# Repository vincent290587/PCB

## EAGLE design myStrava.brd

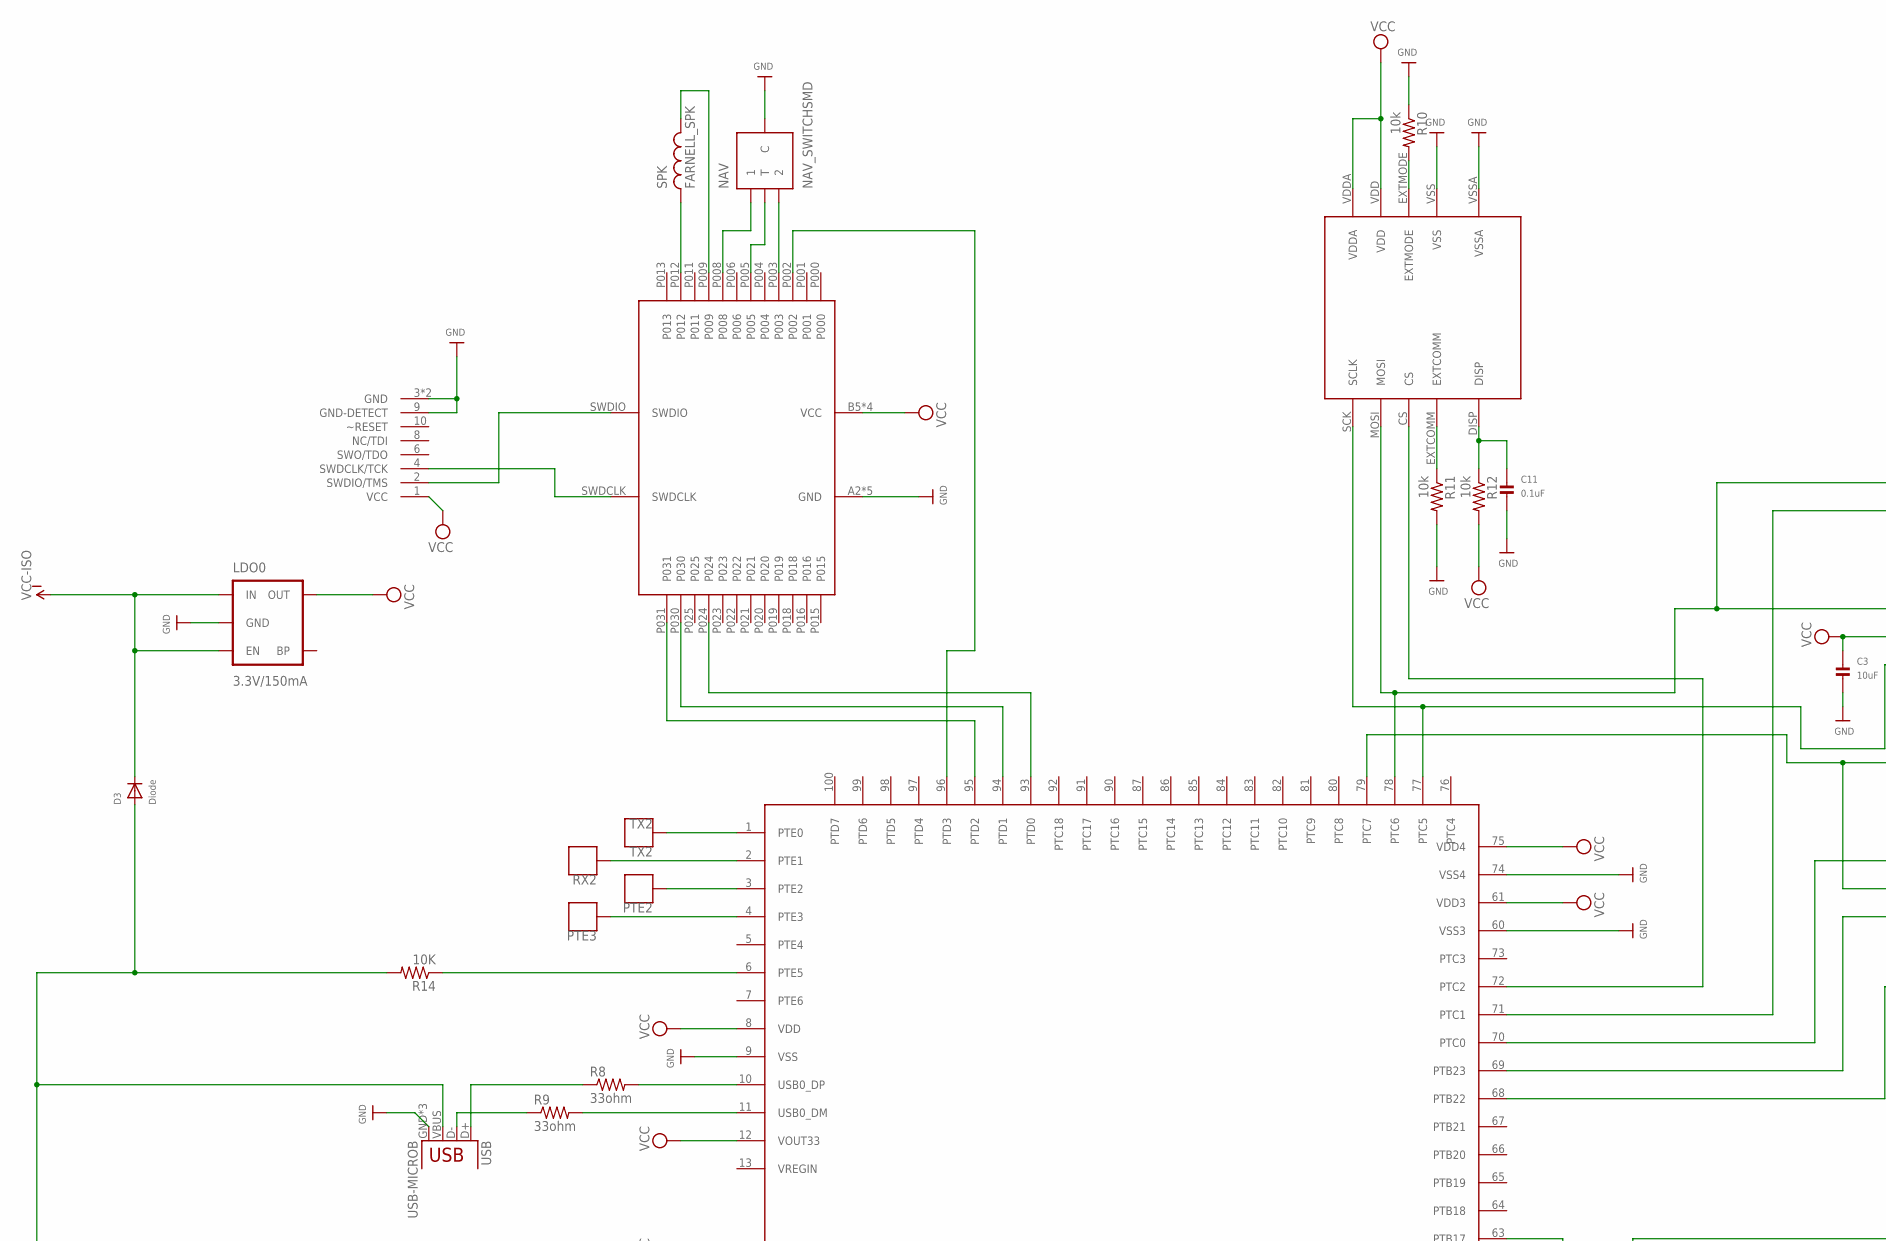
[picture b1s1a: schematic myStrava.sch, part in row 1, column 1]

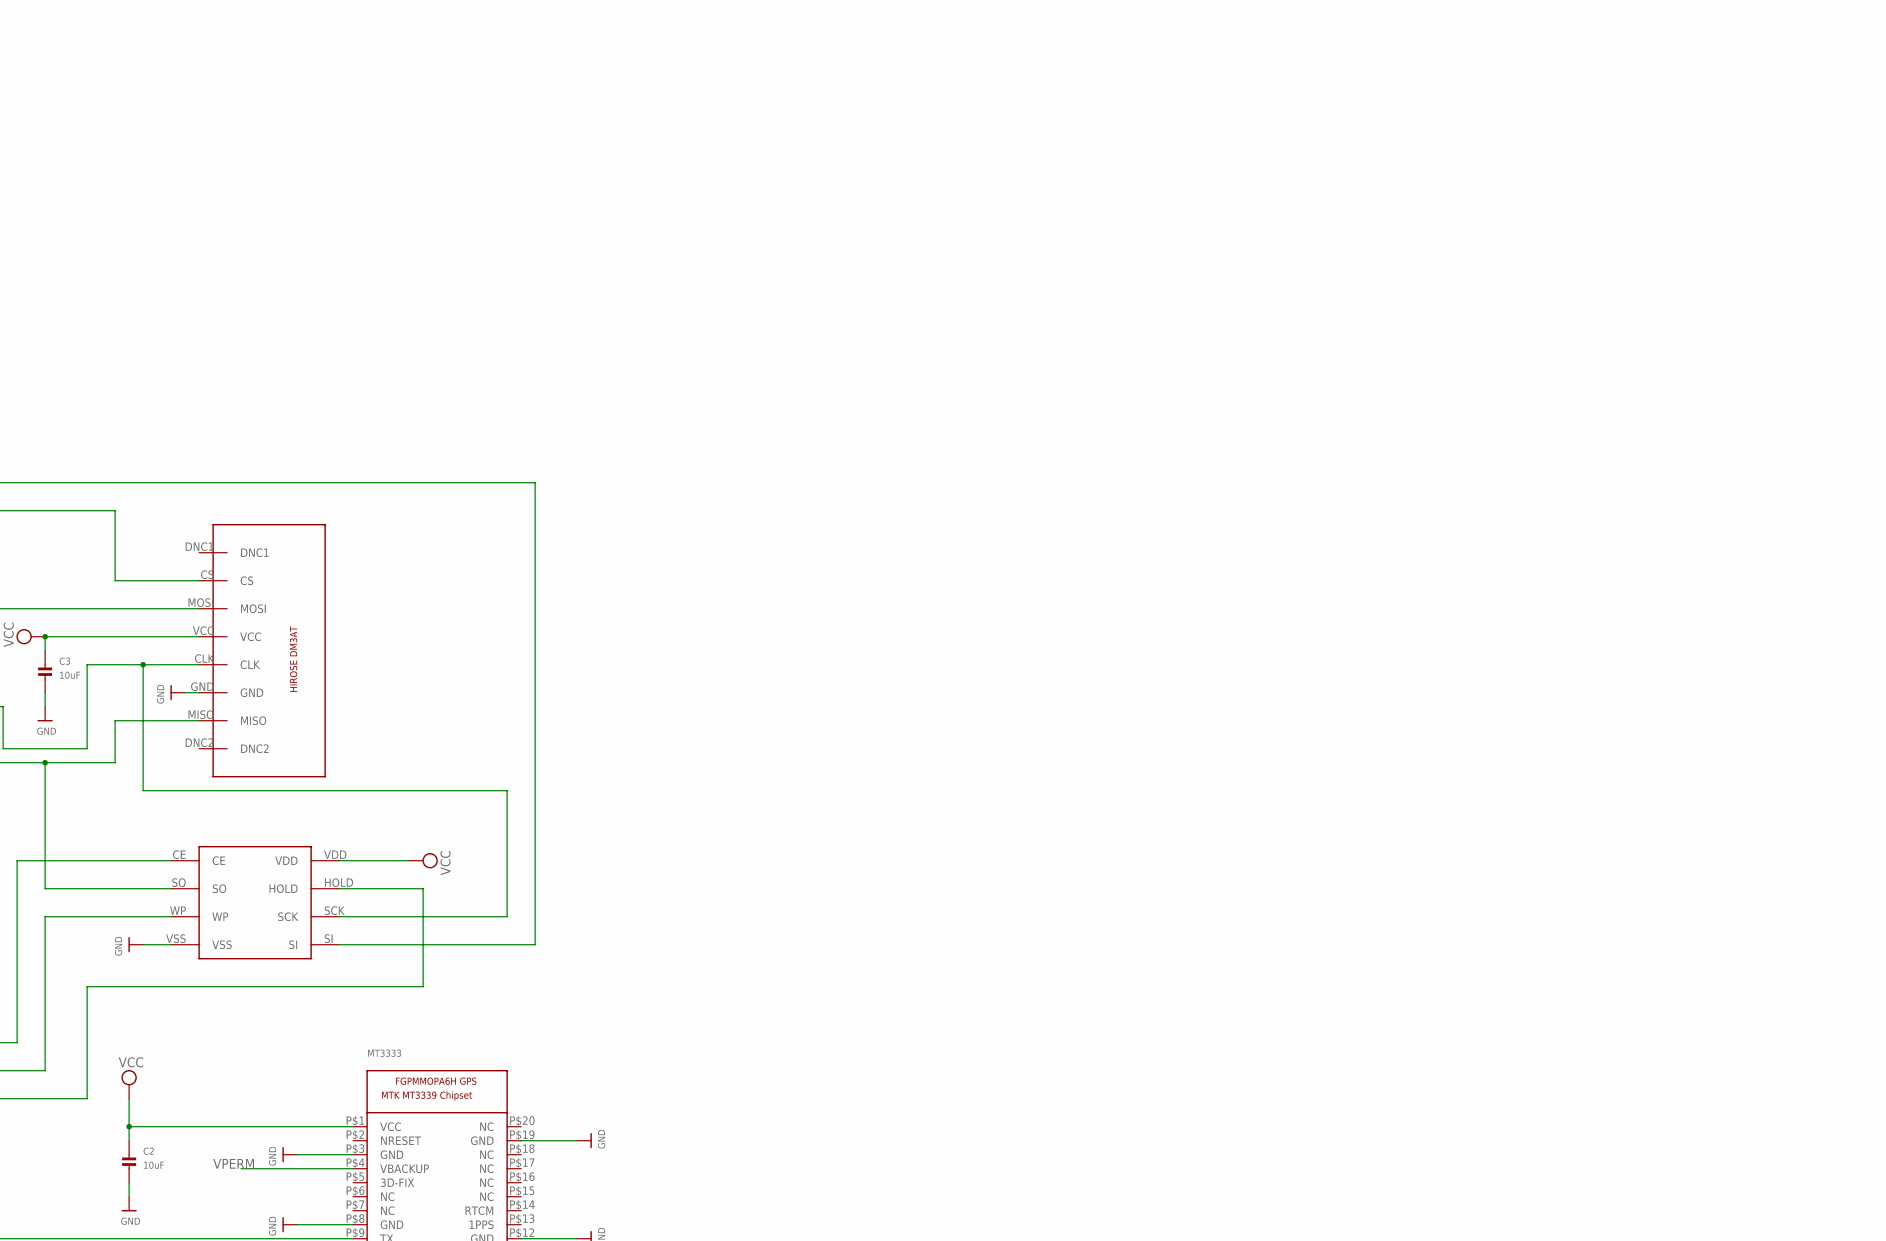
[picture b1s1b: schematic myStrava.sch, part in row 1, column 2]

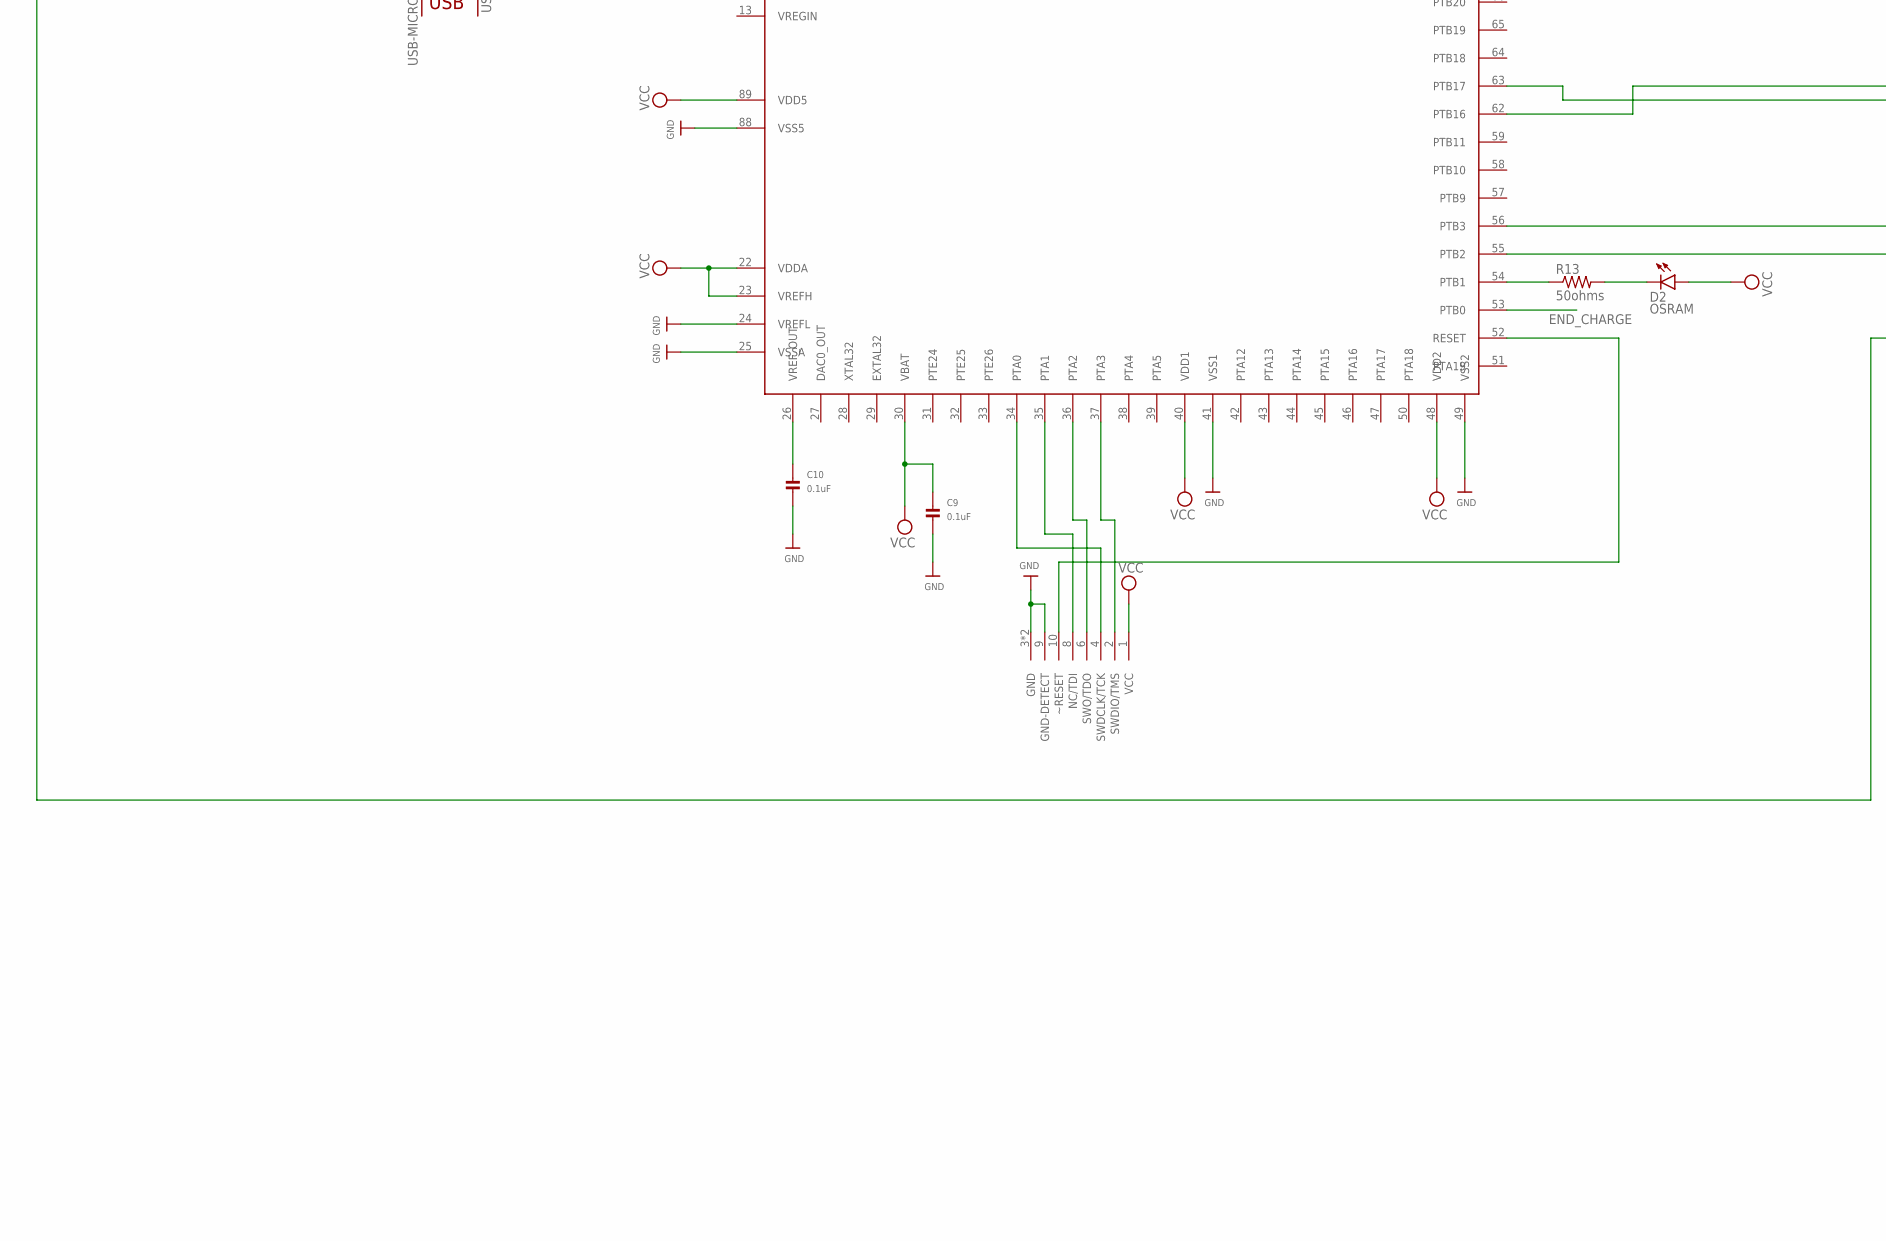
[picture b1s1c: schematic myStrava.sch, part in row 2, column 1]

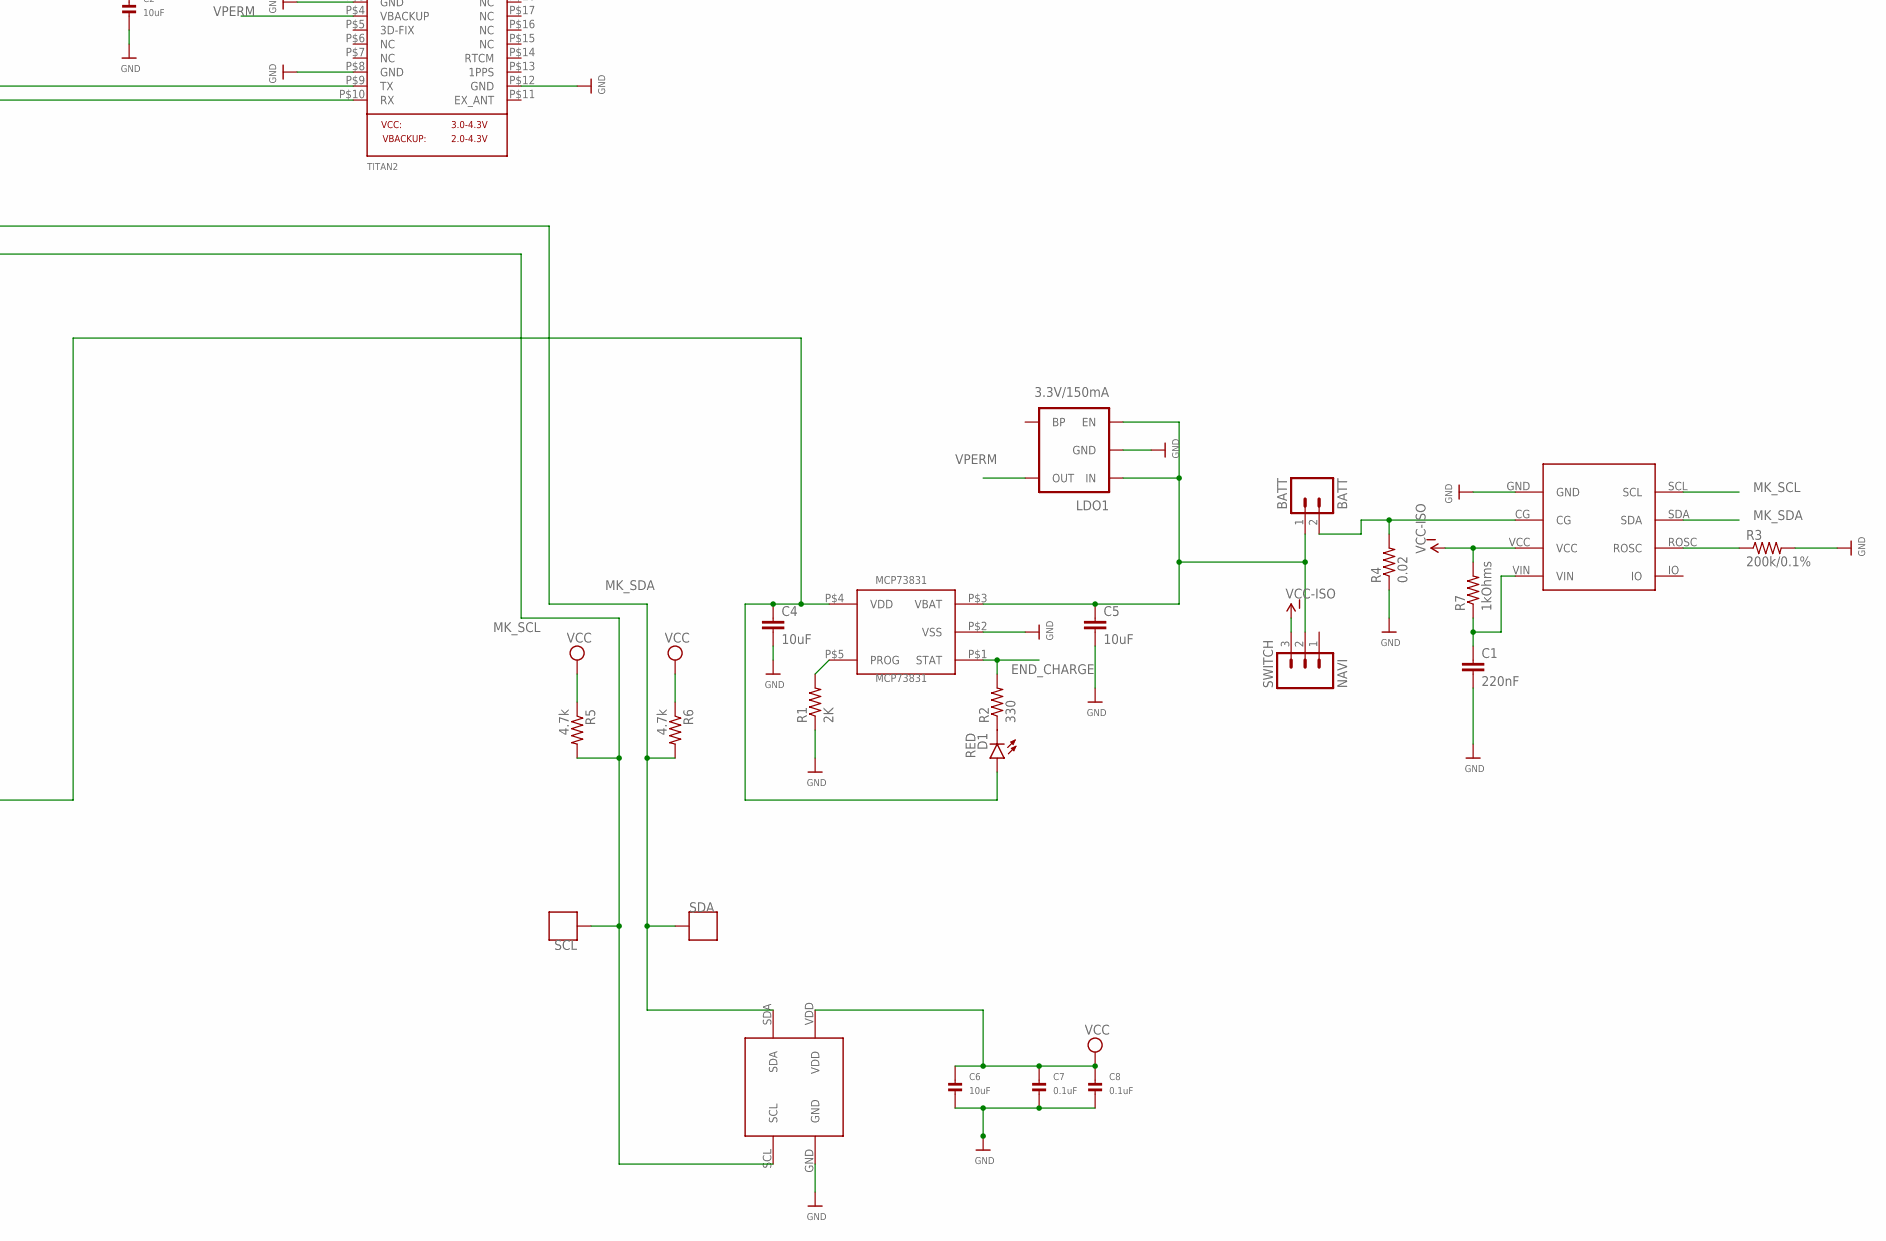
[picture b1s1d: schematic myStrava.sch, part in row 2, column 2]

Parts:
BATT: BATT; 1X02_LONGPADS
C1: 220nF; 1206
C2, C3, C4, C5, C6: 10uF; 1206
C7, C8, C9, C10, C11: 0.1uF; 1206
D1: RED; LED-1206
D2: OSRAM; LED-1206
D3: Diode; SOD-123FL
D52Q: N548
JTAG, JTAG1: 2X5_0.05"_CORTEX_DEBUGTH_NOKEY_UNSHROUDED; 2X5_0.05"_TH_NS
LDO0, LDO1: 3.3V/150mA; SOT23-5
MCP73831: MCP73831; 5PIN_SOT23
MK20DN512: MK20DN512; LQFP-100
MS5637: MS5637
MT3333: TITAN2; FGPMMOPA6H
NAV: NAV_SWITCHSMD; NAV_SWITCH
PTE2, PTE3: MDMK2020T4R7MM; IND-2020
R1: 2K; 1206
R2: 330; 1206
R3: 200k/0.1%; 1206
R4: 0.02; 1206
R5, R6: 4.7k; 1206
R7: 1kOhms; 1206
R8, R9: 33ohm; 0805
R10, R11, R12: 10k; 1206
R13: 50ohms; 1206
R14: 10K; 1206
RX2: MDMK2020T4R7MM; IND-2020
SCL: MDMK2020T4R7MM; IND-2020
SD: DM3AT
SDA: MDMK2020T4R7MM; IND-2020
SHARP: SHARP27
SPK: FARNELL_SPK; IND-2020
SST25: FLASH; SOIC8
STC3100: STC3100
SWITCH: NAVI; 1X03_LOCK
TX2: TX2; IND-2020
USB: USB-MICROB

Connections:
END_CHARGE: MCP73831.P$1 (STAT), MK20DN512.53 (PTB0), R2.2
GND: C1.2, C2.2, C3.2, C4.2, C5.2, C6.2, C7.2, C8.2, C9.2, C10.2, C11.2, D52Q.A2 (GND), D52Q.A3 (GND), D52Q.A4 (GND), D52Q.A5 (GND), D52Q.A6 (GND), JTAG.3 (GND), JTAG.5 (GND), JTAG.9 (GND-DETECT), JTAG1.3 (GND), JTAG1.5 (GND), JTAG1.9 (GND-DETECT), LDO0.2 (GND), LDO1.2 (GND), MCP73831.P$2 (VSS), MK20DN512.9 (VSS), MK20DN512.24 (VREFL), MK20DN512.25 (VSSA), MK20DN512.41 (VSS1), MK20DN512.49 (VSS2), MK20DN512.60 (VSS3), MK20DN512.74 (VSS4), MK20DN512.88 (VSS5), MS5637.GND, MT3333.P$3 (GND), MT3333.P$8 (GND), MT3333.P$12 (GND), MT3333.P$19 (GND), NAV.C, R1.1, R3.2, R4.1, R10.1, R11.2, SD.GND, SHARP.VSS, SHARP.VSSA, SST25.VSS, STC3100.GND, USB.GND, USB.MT1 (GND), USB.MT2 (GND)
MK_DI: MK20DN512.79 (PTC7), SD.MISO, SST25.SO
MK_DO: MK20DN512.78 (PTC6), SD.MOSI, SHARP.MOSI, SST25.SI
MK_RX1: MK20DN512.62 (PTB16), MT3333.P$9 (TX)
MK_RX2: MK20DN512.2 (PTE1), RX2.P$1
MK_SCL: MK20DN512.55 (PTB2), MS5637.SCL, R5.2, SCL.P$1, STC3100.SCL
MK_SCLK: MK20DN512.77 (PTC5), SD.CLK, SHARP.SCK (SCLK), SST25.SCK
MK_SDA: MK20DN512.56 (PTB3), MS5637.SDA, R6.2, SDA.P$1, STC3100.SDA
MK_TX1: MK20DN512.63 (PTB17), MT3333.P$10 (RX)
MK_TX2: MK20DN512.1 (PTE0), TX2.P$1
MK_USB_DETECT: MK20DN512.6 (PTE5), R14.1
unnamed: MK20DN512.71 (PTC1), SD.CS
unnamed: BATT.1, C5.1, LDO1.1 (IN), LDO1.3 (EN), MCP73831.P$3 (VBAT), SWITCH.2
unnamed: D52Q.P012, SPK.P$1 (1)
unnamed: R3.1, STC3100.ROSC
unnamed: C1.1, R7.1, STC3100.VIN
unnamed: BATT.2, R4.2, STC3100.CG
unnamed: D52Q.P009, SPK.P$2 (2)
unnamed: D52Q.P008, NAV.1
unnamed: D52Q.P005, NAV.T
unnamed: D52Q.P003, NAV.2
unnamed: D52Q.SWDIO, JTAG1.2 (SWDIO/TMS)
unnamed: D52Q.SWDCLK, JTAG1.4 (SWDCLK/TCK)
unnamed: D52Q.P024, MK20DN512.93 (PTD0)
unnamed: MK20DN512.69 (PTB23), SST25.WP
unnamed: MCP73831.P$5 (PROG), R1.2
unnamed: D2.C, R13.2
unnamed: D52Q.P030, MK20DN512.94 (PTD1)
unnamed: D1.C, R2.1
unnamed: D52Q.P031, MK20DN512.95 (PTD2)
unnamed: MK20DN512.72 (PTC2), SHARP.CS
unnamed: C10.1, MK20DN512.26 (VREF_OUT)
unnamed: MK20DN512.68 (PTB22), SST25.HOLD
unnamed: R10.2, SHARP.EXTMODE
unnamed: R11.1, SHARP.EXTCOMM
unnamed: C11.1, R12.1, SHARP.DISP
unnamed: MK20DN512.3 (PTE2), PTE2.P$1
unnamed: D52Q.P002, MK20DN512.96 (PTD3)
unnamed: MK20DN512.4 (PTE3), PTE3.P$1
unnamed: MK20DN512.54 (PTB1), R13.1
unnamed: MK20DN512.70 (PTC0), SST25.CE
unnamed: JTAG.10 (~RESET), MK20DN512.52 (RESET)
TCLK: JTAG.4 (SWDCLK/TCK), MK20DN512.34 (PTA0)
TDI: JTAG.8 (NC/TDI), MK20DN512.35 (PTA1)
TDO: JTAG.6 (SWO/TDO), MK20DN512.36 (PTA2)
TMS: JTAG.2 (SWDIO/TMS), MK20DN512.37 (PTA3)
USB1_DM_N: R9.1, USB.D-
USB1_DM_P: R8.1, USB.D+
USB_DM_N: MK20DN512.11 (USB0_DM), R9.2
USB_DM_P: MK20DN512.10 (USB0_DP), R8.2
USB_V+: C4.1, D1.A, D3.A, MCP73831.P$4 (VDD), R14.2, USB.VBUS
VCC: C2.1, C3.1, C6.1, C7.1, C8.1, C9.1, D2.A, D52Q.B5 (VCC), D52Q.B6 (VCC), D52Q.C5 (VCC), D52Q.C6 (VCC), JTAG.1 (VCC), JTAG1.1 (VCC), LDO0.5 (OUT), MK20DN512.8 (VDD), MK20DN512.12 (VOUT33), MK20DN512.22 (VDDA), MK20DN512.23 (VREFH), MK20DN512.30 (VBAT), MK20DN512.40 (VDD1), MK20DN512.48 (VDD2), MK20DN512.61 (VDD3), MK20DN512.75 (VDD4), MK20DN512.89 (VDD5), MS5637.VDD, MT3333.P$1 (VCC), R5.1, R6.1, R12.2, SD.VCC, SHARP.VDD, SHARP.VDDA, SST25.VDD
VCC-ISO: D3.C, LDO0.1 (IN), LDO0.3 (EN), R7.2, STC3100.VCC, SWITCH.3
VPERM: LDO1.5 (OUT), MT3333.P$4 (VBACKUP)

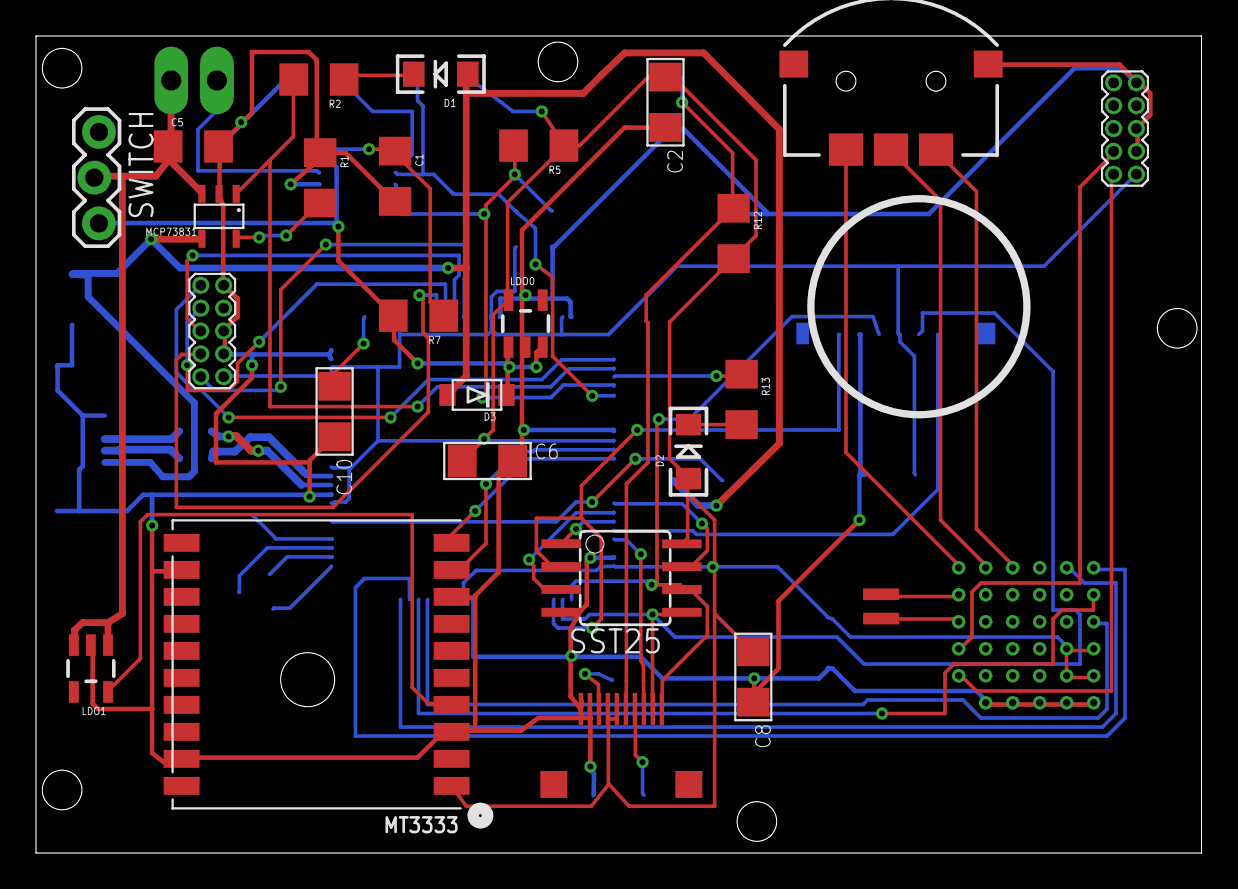
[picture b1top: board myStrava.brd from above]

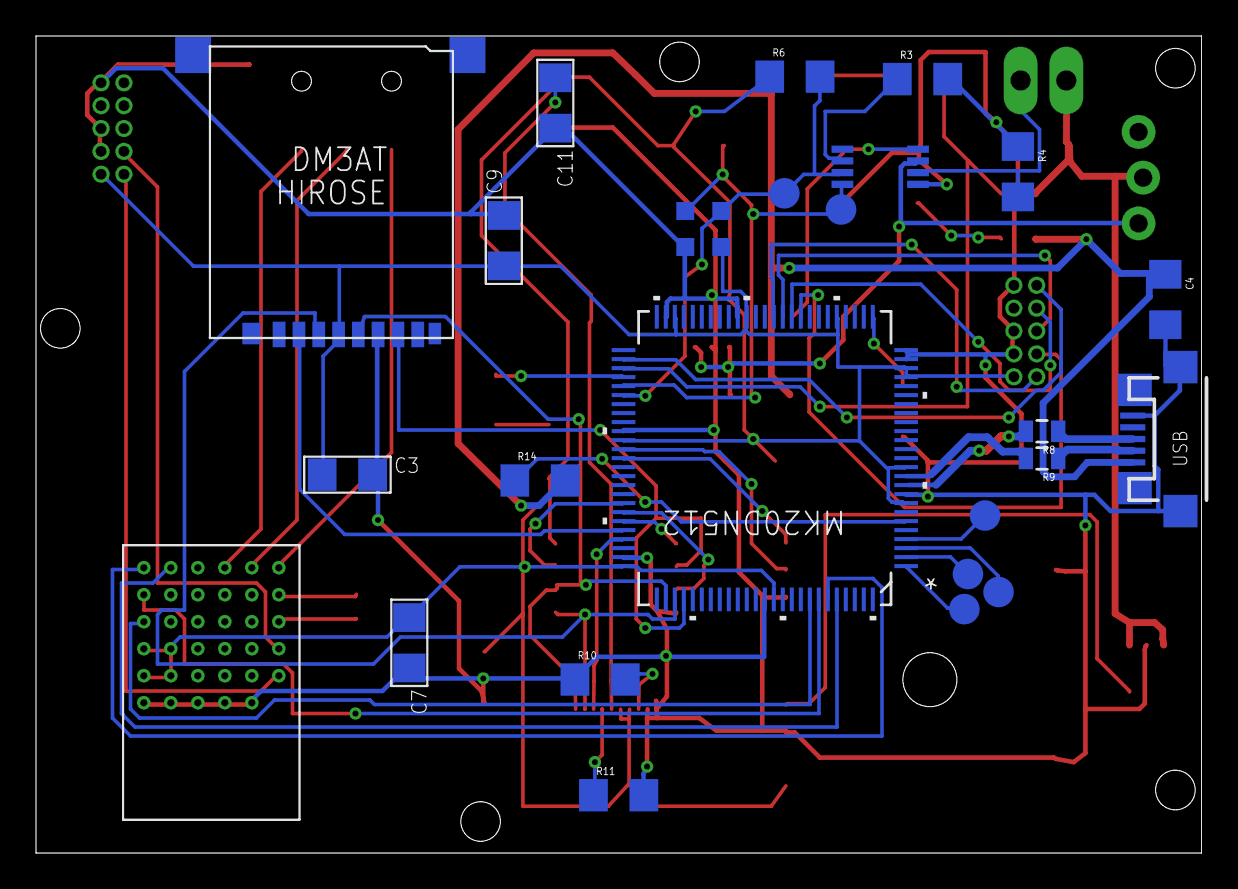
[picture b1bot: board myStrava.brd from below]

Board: 2 copper layers, 64.8 x 45.4 mm, 52 parts (25 on the bottom side), 55 nets.

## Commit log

2015-08-25 Premier commit
2015-09-11 Premiere board complete, manque l'ecran !
2015-10-24 Bare metal !!!
2015-10-26 Routage initial
2015-10-29 Envoi seeedstudio
2015-11-13 Candidat V2
2015-12-06 Avant autoroutage
2016-01-10 Version avec MK64
2016-05-14 Circuit imprime avec bugs
2016-05-14 Modif pour le module D52Q
2016-05-31 Recablage du D52 pour simplifier
2016-10-19 Envoi a OSH park
2016-10-21 Ajout du M8 en face inferieure
2016-10-21 Modif d'une via

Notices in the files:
parts and their libraries:
SparkFun-Capacitors: Licensing: Creative Commons ShareAlike 4.0 International - https://creativecommons.org/licenses/by-sa/4.0
